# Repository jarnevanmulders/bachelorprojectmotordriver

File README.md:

# Bachelor Project Motor Driver

Features:
* Two IO Expanders TCA9554A with I2C address 0x38 and 0x39
* Two Motor Drivers TB6612FNG

Information:
* Possible to connect four DC Motors to the board
* Eight IO Pins adjustable with IO Expander (0x39)

Motor Control:
* Direction of the motors adjustable with IO Expander (0x38)
* Speed of the motor adjustable with the PWM connector

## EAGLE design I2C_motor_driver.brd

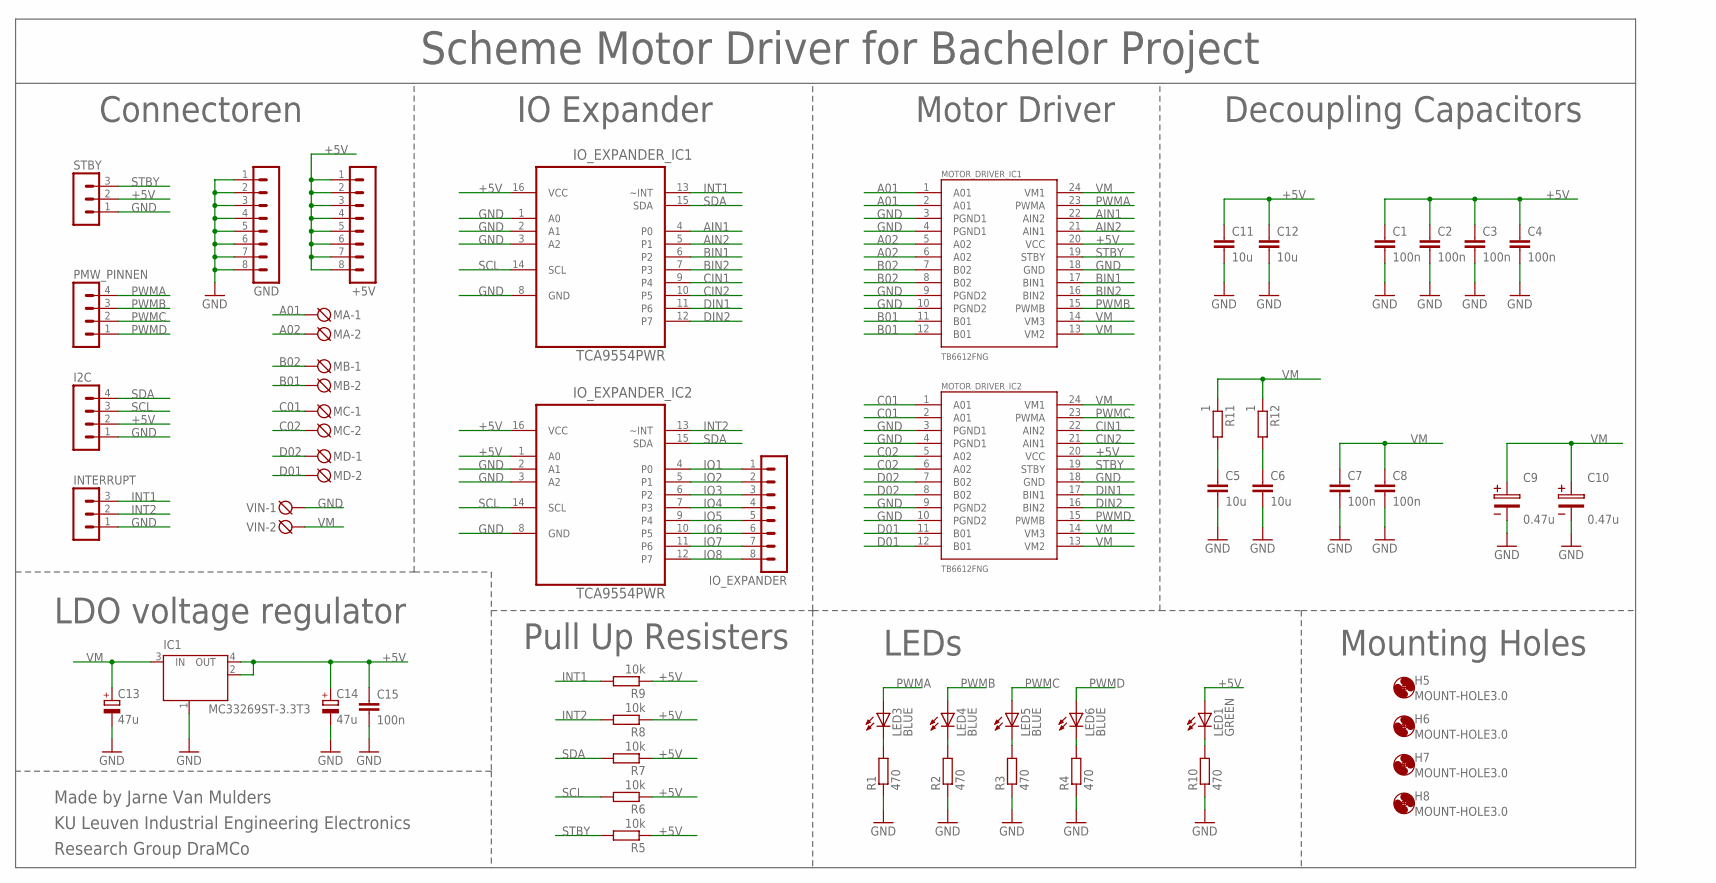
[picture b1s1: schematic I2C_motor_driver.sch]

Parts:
+5V: MA08-1
C1, C2, C3, C4, C7, C8, C15: 100n; C1206K
C5, C6, C11, C12: 10u; C1206K
C9, C10: 0.47u; 2.6X1.6X1(BXCXA)
C13, C14: 47u; PANASONIC_D
GND: MA08-1
H5, H6, H7, H8: MOUNT-HOLE3.0; 3,0
I2C: MA04-1
IC1: MC33269ST-3.3T3; SOT223
INTERRUPT: MA03-1
IO_EXPANDER: MA08-1
IO_EXPANDER_IC1, IO_EXPANDER_IC2: TCA9554PWR; SOP65P640X120-16N
LED1: GREEN; SML0805
LED3, LED4, LED5, LED6: BLUE; SML0805
MA: DG3XX-02-5.0; DG306-5.0-02P
MB: DG3XX-02-5.0; DG306-5.0-02P
MC: DG3XX-02-5.0; DG306-5.0-02P
MD: DG3XX-02-5.0; DG306-5.0-02P
MOTOR_DRIVER_IC1, MOTOR_DRIVER_IC2: TB6612FNG; SSOP24
PMW_PINNEN: MA04-1
R1, R2, R3, R4, R10: 470; R1206
R5, R6, R7, R8, R9: 10k; R1206
R11, R12: 1; R1206
STBY: MA03-1
VIN: DG3XX-02-5.0; DG306-5.0-02P

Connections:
+5V: +5V.1, +5V.2, +5V.3, +5V.4, +5V.5, +5V.6, +5V.7, +5V.8, C1.1, C2.1, C3.1, C4.1, C11.1, C12.1, C14.+, C15.1, I2C.2, IC1.2 (OUT), IC1.4 (OUT), IO_EXPANDER_IC1.16 (VCC), IO_EXPANDER_IC2.1 (A0), IO_EXPANDER_IC2.16 (VCC), LED1.A, MOTOR_DRIVER_IC1.20 (VCC), MOTOR_DRIVER_IC2.20 (VCC), R5.1, R6.1, R7.1, R8.1, R9.1, STBY.2
A01: MA.1, MOTOR_DRIVER_IC1.1 (A01), MOTOR_DRIVER_IC1.2 (A01)
A02: MA.2, MOTOR_DRIVER_IC1.5 (A02), MOTOR_DRIVER_IC1.6 (A02)
AIN1: IO_EXPANDER_IC1.4 (P0), MOTOR_DRIVER_IC1.22 (AIN2)
AIN2: IO_EXPANDER_IC1.5 (P1), MOTOR_DRIVER_IC1.21 (AIN1)
B01: MB.2, MOTOR_DRIVER_IC1.11 (B01), MOTOR_DRIVER_IC1.12 (B01)
B02: MB.1, MOTOR_DRIVER_IC1.7 (B02), MOTOR_DRIVER_IC1.8 (B02)
BIN1: IO_EXPANDER_IC1.6 (P2), MOTOR_DRIVER_IC1.17 (BIN1)
BIN2: IO_EXPANDER_IC1.7 (P3), MOTOR_DRIVER_IC1.16 (BIN2)
C01: MC.1, MOTOR_DRIVER_IC2.1 (A01), MOTOR_DRIVER_IC2.2 (A01)
C02: MC.2, MOTOR_DRIVER_IC2.5 (A02), MOTOR_DRIVER_IC2.6 (A02)
CIN1: IO_EXPANDER_IC1.9 (P4), MOTOR_DRIVER_IC2.22 (AIN2)
CIN2: IO_EXPANDER_IC1.10 (P5), MOTOR_DRIVER_IC2.21 (AIN1)
D01: MD.2, MOTOR_DRIVER_IC2.11 (B01), MOTOR_DRIVER_IC2.12 (B01)
D02: MD.1, MOTOR_DRIVER_IC2.7 (B02), MOTOR_DRIVER_IC2.8 (B02)
DIN1: IO_EXPANDER_IC1.11 (P6), MOTOR_DRIVER_IC2.17 (BIN1)
DIN2: IO_EXPANDER_IC1.12 (P7), MOTOR_DRIVER_IC2.16 (BIN2)
GND: C1.2, C2.2, C3.2, C4.2, C5.2, C6.2, C7.2, C8.2, C9.2, C10.2, C11.2, C12.2, C13.-, C14.-, C15.2, GND.1, GND.2, GND.3, GND.4, GND.5, GND.6, GND.7, GND.8, I2C.1, IC1.1 (GND/ADJ), INTERRUPT.1, IO_EXPANDER_IC1.1 (A0), IO_EXPANDER_IC1.2 (A1), IO_EXPANDER_IC1.3 (A2), IO_EXPANDER_IC1.8 (GND), IO_EXPANDER_IC2.2 (A1), IO_EXPANDER_IC2.3 (A2), IO_EXPANDER_IC2.8 (GND), MOTOR_DRIVER_IC1.3 (PGND1), MOTOR_DRIVER_IC1.4 (PGND1), MOTOR_DRIVER_IC1.9 (PGND2), MOTOR_DRIVER_IC1.10 (PGND2), MOTOR_DRIVER_IC1.18 (GND), MOTOR_DRIVER_IC2.3 (PGND1), MOTOR_DRIVER_IC2.4 (PGND1), MOTOR_DRIVER_IC2.9 (PGND2), MOTOR_DRIVER_IC2.10 (PGND2), MOTOR_DRIVER_IC2.18 (GND), R1.1, R2.1, R3.1, R4.1, R10.1, STBY.1, VIN.1
INT1: INTERRUPT.3, IO_EXPANDER_IC1.13 (~INT), R9.2
INT2: INTERRUPT.2, IO_EXPANDER_IC2.13 (~INT), R8.2
IO1: IO_EXPANDER.1, IO_EXPANDER_IC2.4 (P0)
IO2: IO_EXPANDER.2, IO_EXPANDER_IC2.5 (P1)
IO3: IO_EXPANDER.3, IO_EXPANDER_IC2.6 (P2)
IO4: IO_EXPANDER.4, IO_EXPANDER_IC2.7 (P3)
IO5: IO_EXPANDER.5, IO_EXPANDER_IC2.9 (P4)
IO6: IO_EXPANDER.6, IO_EXPANDER_IC2.10 (P5)
IO7: IO_EXPANDER.7, IO_EXPANDER_IC2.11 (P6)
IO8: IO_EXPANDER.8, IO_EXPANDER_IC2.12 (P7)
unnamed: C5.1, R11.2
unnamed: C6.1, R12.2
unnamed: LED1.C, R10.2
unnamed: LED3.C, R1.2
unnamed: LED4.C, R2.2
unnamed: LED5.C, R3.2
unnamed: LED6.C, R4.2
PWMA: LED3.A, MOTOR_DRIVER_IC1.23 (PWMA), PMW_PINNEN.4
PWMB: LED4.A, MOTOR_DRIVER_IC1.15 (PWMB), PMW_PINNEN.3
PWMC: LED5.A, MOTOR_DRIVER_IC2.23 (PWMA), PMW_PINNEN.2
PWMD: LED6.A, MOTOR_DRIVER_IC2.15 (PWMB), PMW_PINNEN.1
SCL: I2C.3, IO_EXPANDER_IC1.14 (SCL), IO_EXPANDER_IC2.14 (SCL), R6.2
SDA: I2C.4, IO_EXPANDER_IC1.15 (SDA), IO_EXPANDER_IC2.15 (SDA), R7.2
STBY: MOTOR_DRIVER_IC1.19 (STBY), MOTOR_DRIVER_IC2.19 (STBY), R5.2, STBY.3
VM: C7.1, C8.1, C9.1, C10.1, C13.+, IC1.3 (IN), MOTOR_DRIVER_IC1.13 (VM2), MOTOR_DRIVER_IC1.14 (VM3), MOTOR_DRIVER_IC1.24 (VM1), MOTOR_DRIVER_IC2.13 (VM2), MOTOR_DRIVER_IC2.14 (VM3), MOTOR_DRIVER_IC2.24 (VM1), R11.1, R12.1, VIN.2

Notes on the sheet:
Connectoren
LEDs
LDO voltage regulator
IO Expander
Motor Driver
Decoupling Capacitors
Mounting Holes
Pull Up Resisters
Scheme Motor Driver for Bachelor Project
Made by Jarne Van Mulders
KU Leuven Industrial Engineering Electronics
Research Group DraMCo

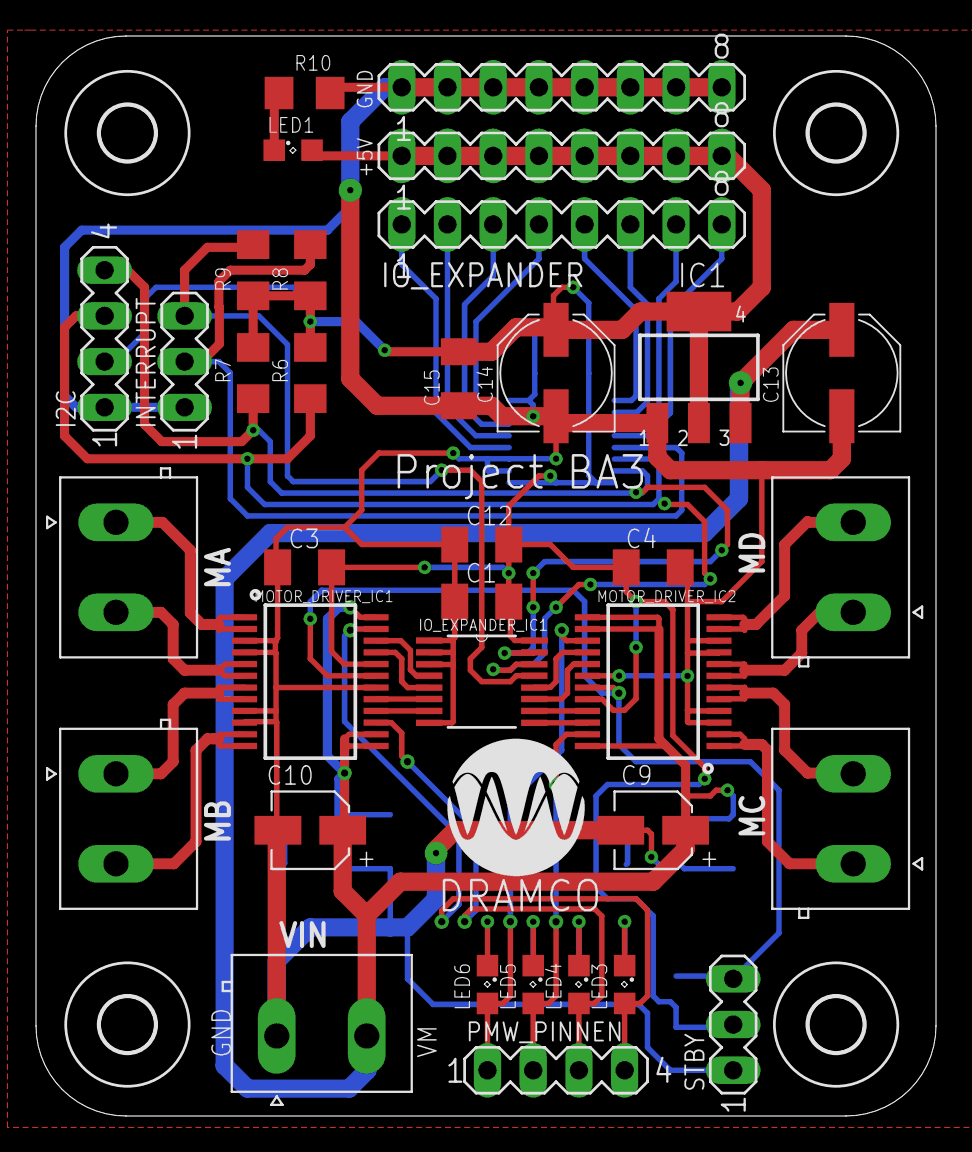
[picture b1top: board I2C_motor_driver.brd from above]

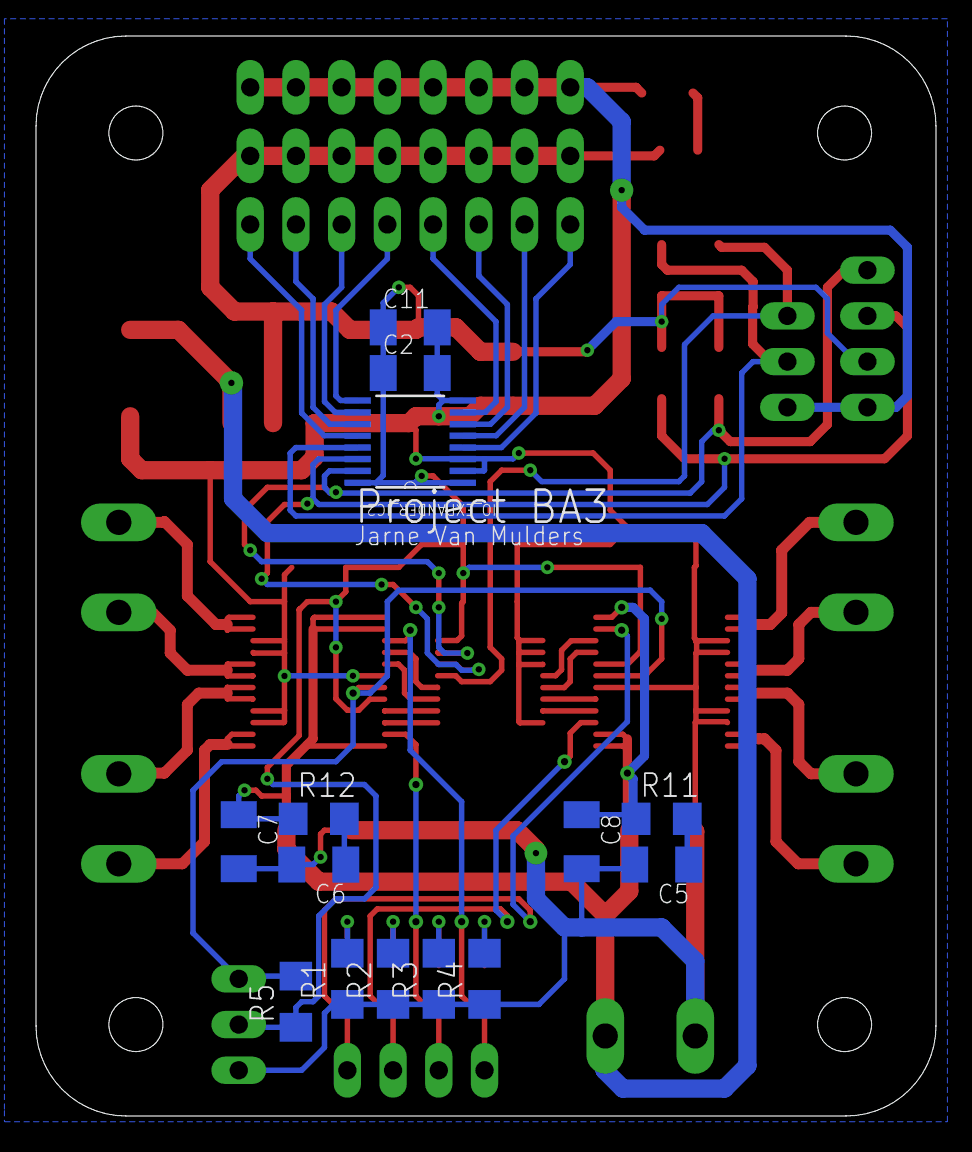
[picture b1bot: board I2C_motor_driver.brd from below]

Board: 2 copper layers, 50.0 x 60.0 mm, 53 parts (14 on the bottom side), 43 nets.

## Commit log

2018-10-21 Creating Motor Driver Board
2018-10-21 Update README.md
    Update README.md
2018-10-21 Update Readme.md.gitattributes
    Removed Readme.md.gitattributes

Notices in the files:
parts and their libraries:
Kondensatoren: Copyright: Würth Elektronik
SparkFun-IC-Special-Function: Licensing: Creative Commons ShareAlike 4.0 International - https://creativecommons.org/licenses/by-sa/4.0
